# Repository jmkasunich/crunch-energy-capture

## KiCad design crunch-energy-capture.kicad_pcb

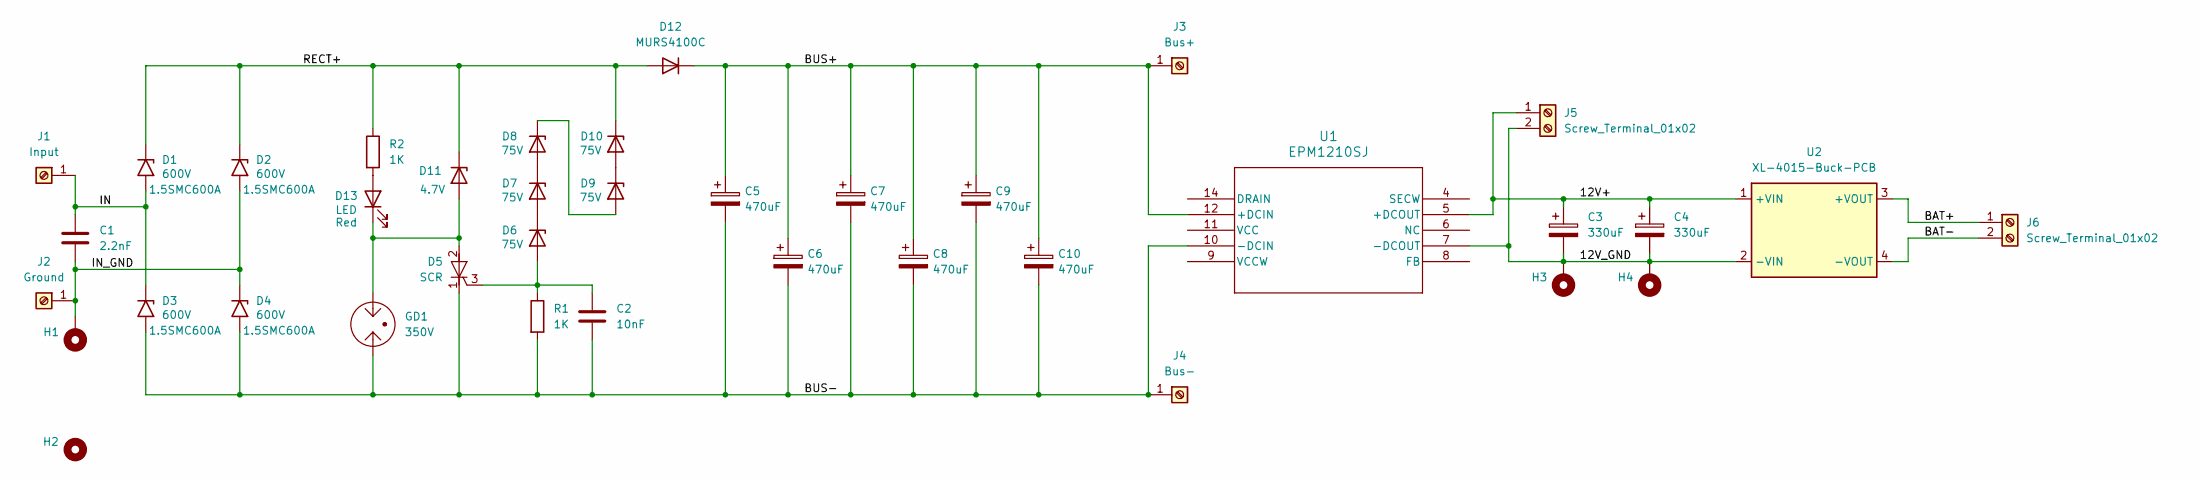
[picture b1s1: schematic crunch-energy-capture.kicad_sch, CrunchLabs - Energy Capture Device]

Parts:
C1: 2.2nF; C_Rect_L18.0mm_W5.0mm_P15.00mm_FKS3_FKP3; MPN 222PPB162K; Digi-Key_PN 1572-1358-ND
C2: 10nF; C_0805_2012Metric_Pad1.18x1.45mm_HandSolder
C3, C4: 330uF; CP_Radial_D8.0mm_P3.50mm; Voltage 25V; MPN A750KS337M1EAAE018; Digi-Key_PN 399-A750KS337M1EAAE018-ND
C5, C6, C7, C8, C9, C10: 470uF; CP_Radial_D35.0mm_P10.00mm_SnapIn; Voltage 450V
D1, D2, D3, D4: 600V; D_SMC_Handsoldering; MPN 1.5SMC600A; Digi-Key_PN 18-1.5SMC600ACT-ND
D5: SCR; TO-252-2; MPN MCR12DSNT4G; Digi-Key_PN MCR12DSNT4GOSCT-ND
D6, D7, D8, D9, D10: BZT52B75; D_SOD-123F; Voltage 75V; MPN BZT52B75 RHG; Digi-Key_PN 1801-BZT52B75RHGCT-ND
D11: 1SMB5917; D_SMB_Handsoldering; Voltage 4.7V; MPN 1SMB5917BT3G; Digi-Key_PN 1SMB5917BT3GOSCT-ND
D12: MURS4100C; D_SMC_Handsoldering; MPN MURS4100C; Digi-Key_PN 31-MURS4100CCT-ND
D13: LED; LED_Kingbright-SMD3528_3.5x2.8mm; MPN AA3528LSECKT/J3; Digi-Key_PN 754-2068-1-ND
GD1: 350V; GDT_Bourns_2053_SM; MPN 2053-35-SM-RPLF; Digi-Key_PN 118-2053-35-SM-RPLFCT-ND
H1, H3, H4: MountingHole_Pad; MountingHole_3.5mm_Pad_TopBottom
H2: MountingHole; MountingHole_3.5mm
J1: Input; KEYSTONE_7693
J2: Ground; KEYSTONE_7693
J3: Bus+; KEYSTONE_7693
J4: Bus-; KEYSTONE_7693
J5, J6: Screw_Terminal_01x02; TerminalBlock_MetzConnect_Type011_RT05502HBLC_1x02_P5.00mm_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
R1, R2: 1K; R_0805_2012Metric_Pad1.20x1.40mm_HandSolder
U1: EPM1210SJ; EPM1210SJ_TMA; MPN EPM1210SJ; Digi-Key_PN MT7382-ND
U2: XL-4015-Buck-PCB; XL4015-Buck-Module

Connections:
/12V+: C3.1, C4.1, J5.1, U1.5 (+DCOUT), U2.1 (+VIN)
/12V_GND: C3.2, C4.2, H3.1, H4.1, J5.2, U1.7 (-DCOUT), U2.2 (-VIN)
/BAT+: J6.1, U2.3 (+VOUT)
/BAT-: J6.2, U2.4 (-VOUT)
/BUS+: C5.1, C6.1, C7.1, C8.1, C9.1, C10.1, D12.1 (K), J3.1, U1.12 (+DCIN)
/BUS-: C2.2, C5.2, C6.2, C7.2, C8.2, C9.2, C10.2, D3.2 (A2), D4.2 (A2), D5.1 (K), GD1.1, J4.1, R1.2, U1.10 (-DCIN)
/IN: C1.1, D1.2 (A2), D3.1 (A1), J1.1
/IN_GND: C1.2, D2.2 (A2), D4.1 (A1), H1.1, J2.1
/RECT+: D1.1 (A1), D2.1 (A1), D10.1 (K), D11.1 (K), D12.2 (A), R2.1
unnamed: C2.1, D5.3 (G), D6.2 (A), R1.1
unnamed: D6.1 (K), D7.2 (A)
unnamed: D7.1 (K), D8.2 (A)
unnamed: D8.1 (K), D9.2 (A)
unnamed: D9.1 (K), D10.2 (A)
unnamed: D5.2 (A), D11.2 (A), D13.1 (K), GD1.3
unnamed: D13.2 (A), R2.2

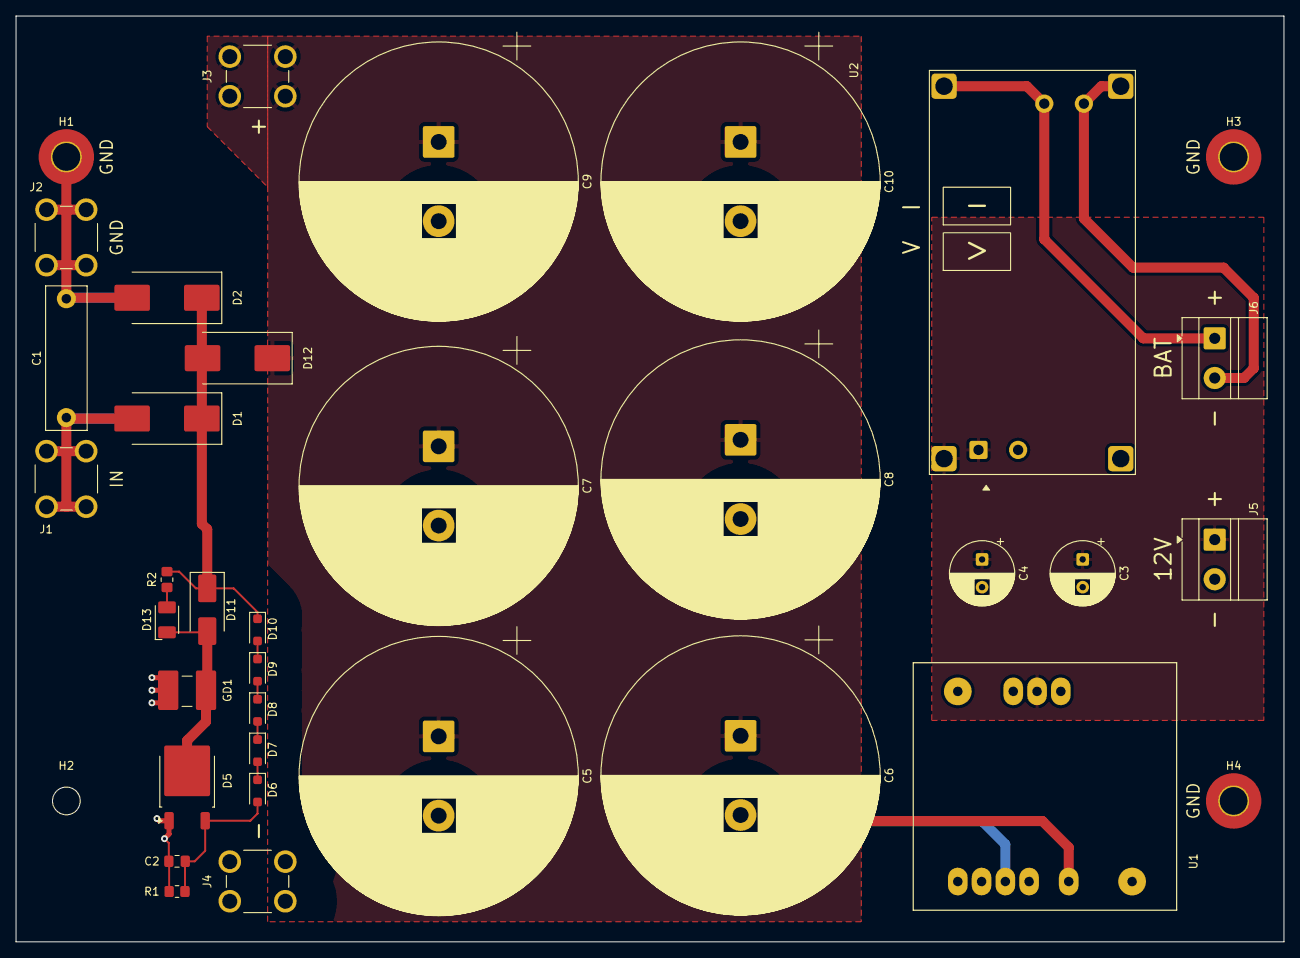
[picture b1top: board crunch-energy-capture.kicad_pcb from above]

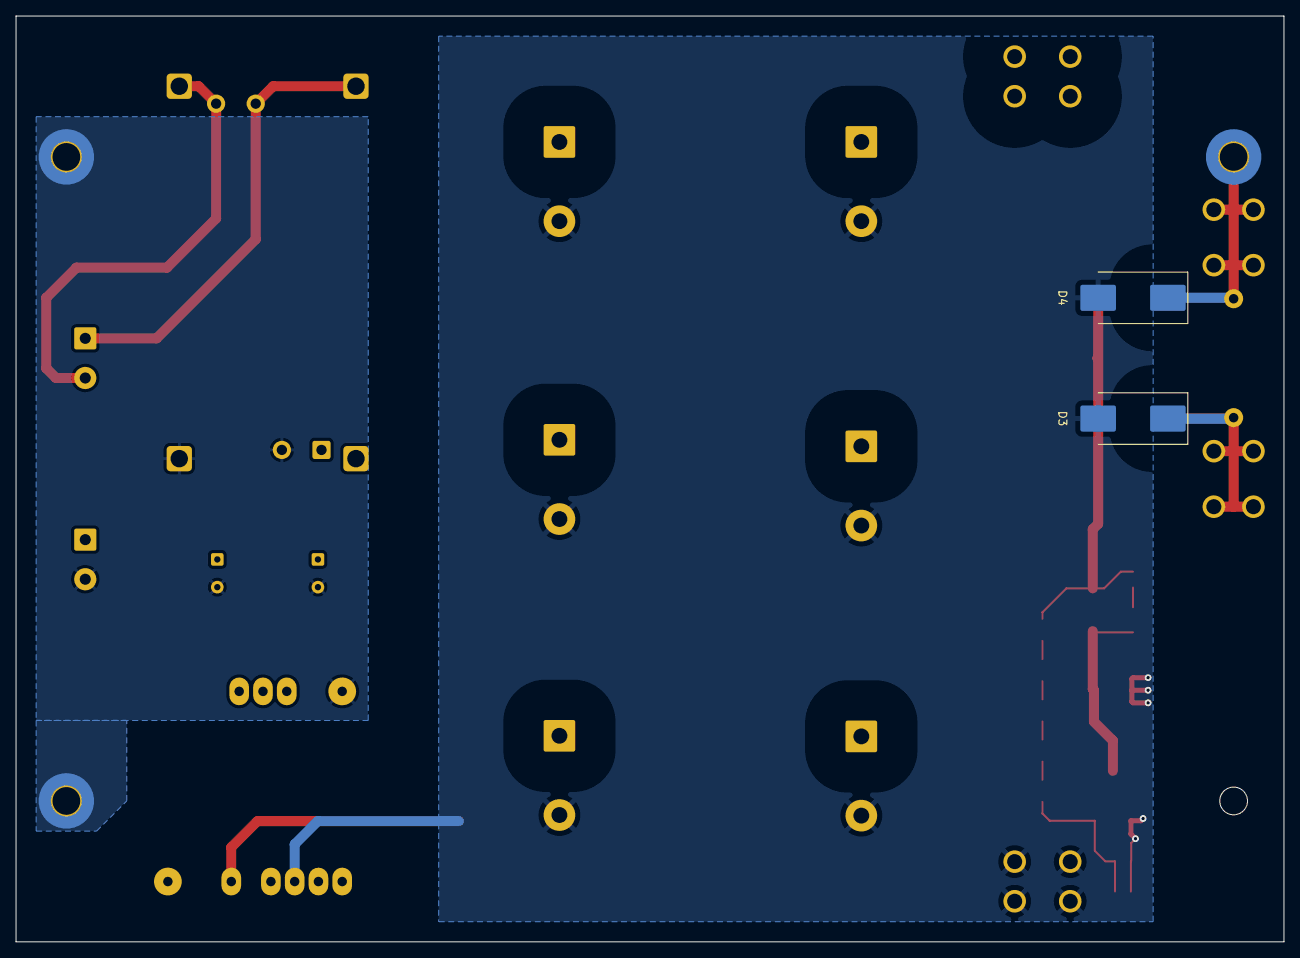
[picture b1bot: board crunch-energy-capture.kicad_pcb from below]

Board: 2 copper layers, 160.0 x 116.8 mm, 38 parts (2 on the bottom side), 16 nets.

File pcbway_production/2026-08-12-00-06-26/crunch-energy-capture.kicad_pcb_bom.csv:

Designator,Quantity,Value,Footprint,Package,MPN,DNP,Mount_Type,Description,Digi-Key_PN,MFG,Voltage,Sim.Device,Sim.Pins,Brightness,ViewAngle,Color
C1,1,2.2nF,C_Rect_L18.0mm_W5.0mm_P15.00mm_FKS3_FKP3,,222PPB162K,,tht,Unpolarized capacitor,1572-1358-ND,ILLINOIS CAPACITOR,,,,,,
"C10, C5, C6, C7, C8, C9",6,470uF,CP_Radial_D35.0mm_P10.00mm_SnapIn,,,,tht,"470uF, 450V Aluminum Electrolytic Capacitor, 35mm dia, 10mm pin spacing",,,450V,,,,,
C2,1,10nF,C_0805_2012Metric_Pad1.18x1.45mm_HandSolder,,,,smt,Unpolarized capacitor,,,,,,,,
"C3, C4",2,330uF,CP_Radial_D8.0mm_P3.50mm,,A750KS337M1EAAE018,,tht,"330uF, 25V Polymer Capacitor",399-A750KS337M1EAAE018-ND,Kemet,25V,,,,,
"D1, D2, D3, D4",4,600V,D_SMC_Handsoldering,,  1.5SMC600A,,smt,"1500W unidirectional TVS diode, DO214AB",18-1.5SMC600ACT-ND,LITTELFUSE INC (VA),,,,,,
"D10, D6, D7, D8, D9",5,BZT52B75,D_SOD-123F,,BZT52B75 RHG,,smt,"500mW Zener Diode, SOD-123F",1801-BZT52B75RHGCT-ND,Tiawan Semiconductor,75V,,,,,
D11,1,1SMB5917,D_SMB_Handsoldering,,1SMB5917BT3G,,smt,"3000mW Zener Diode, SMB",1SMB5917BT3GOSCT-ND,OnSemi,4.7V,,,,,
D12,1,MURS4100C,D_SMC_Handsoldering,,MURS4100C,,smt,"1000V 5A Soft Recovery Ultrafast Rectifier Diode, DO-201AD",31-MURS4100CCT-ND,Diodes Inc,,D,1=K 2=A,,,
D13,1,LED,LED_Kingbright-SMD3528_3.5x2.8mm,,AA3528LSECKT/J3,,smt,Light emitting diode,754-2068-1-ND,KingBright,,,1=K 2=A,120,120,Red
D5,1,SCR,TO-252-2,,MCR12DSNT4G,,smt,"Silicon controlled rectifier, cathode/anode/gate",MCR12DSNT4GOSCT-ND,LITTELFUSE INC (VA),,,,,,
GD1,1,350V,GDT_Bourns_2053_SM,,2053-35-SM-RPLF,,tht,Gas Discharge Tube with 2 Pins,118-2053-35-SM-RPLFCT-ND,"Bourns, Inc",,,,,,
J1,1,Input,KEYSTONE_7693,,,,tht,"Generic screw terminal, single row, 01x01, script generated (kicad-library-utils/schlib/autogen/connector/)",,,,,,,,
J2,1,Ground,KEYSTONE_7693,,,,tht,"Generic screw terminal, single row, 01x01, script generated (kicad-library-utils/schlib/autogen/connector/)",,,,,,,,
J3,1,Bus+,KEYSTONE_7693,,,,tht,"Generic screw terminal, single row, 01x01, script generated (kicad-library-utils/schlib/autogen/connector/)",,,,,,,,
J4,1,Bus-,KEYSTONE_7693,,,,tht,"Generic screw terminal, single row, 01x01, script generated (kicad-library-utils/schlib/autogen/connector/)",,,,,,,,
"J5, J6",2,Screw_Terminal_01x02,TerminalBlock_MetzConnect_Type011_RT05502HBLC_1x02_P5.00mm_Horizontal,,,,tht,"Generic screw terminal, single row, 01x02, script generated (kicad-library-utils/schlib/autogen/connector/)",,,,,,,,
"R1, R2",2,1K,R_0805_2012Metric_Pad1.20x1.40mm_HandSolder,,,,smt,Resistor,,,,,,,,
U1,1,EPM1210SJ,EPM1210SJ_TMA,,EPM1210SJ,,tht,"Isolated DC-DC converter, wide input range. 12V output, 12W, 110-450V input",MT7382-ND,Tamura,,,,,,
U2,1,XL-4015-Buck-PCB,XL4015-Buck-Module,,,,tht,"Non-isolated Buck Converter PCB, XL4015 chip, 0-36V, 0-5A, Amazon",,,,,,,,
